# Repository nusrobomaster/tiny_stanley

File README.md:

# tiny_stanley
A minaturised version of our Standard robot, Stanley!

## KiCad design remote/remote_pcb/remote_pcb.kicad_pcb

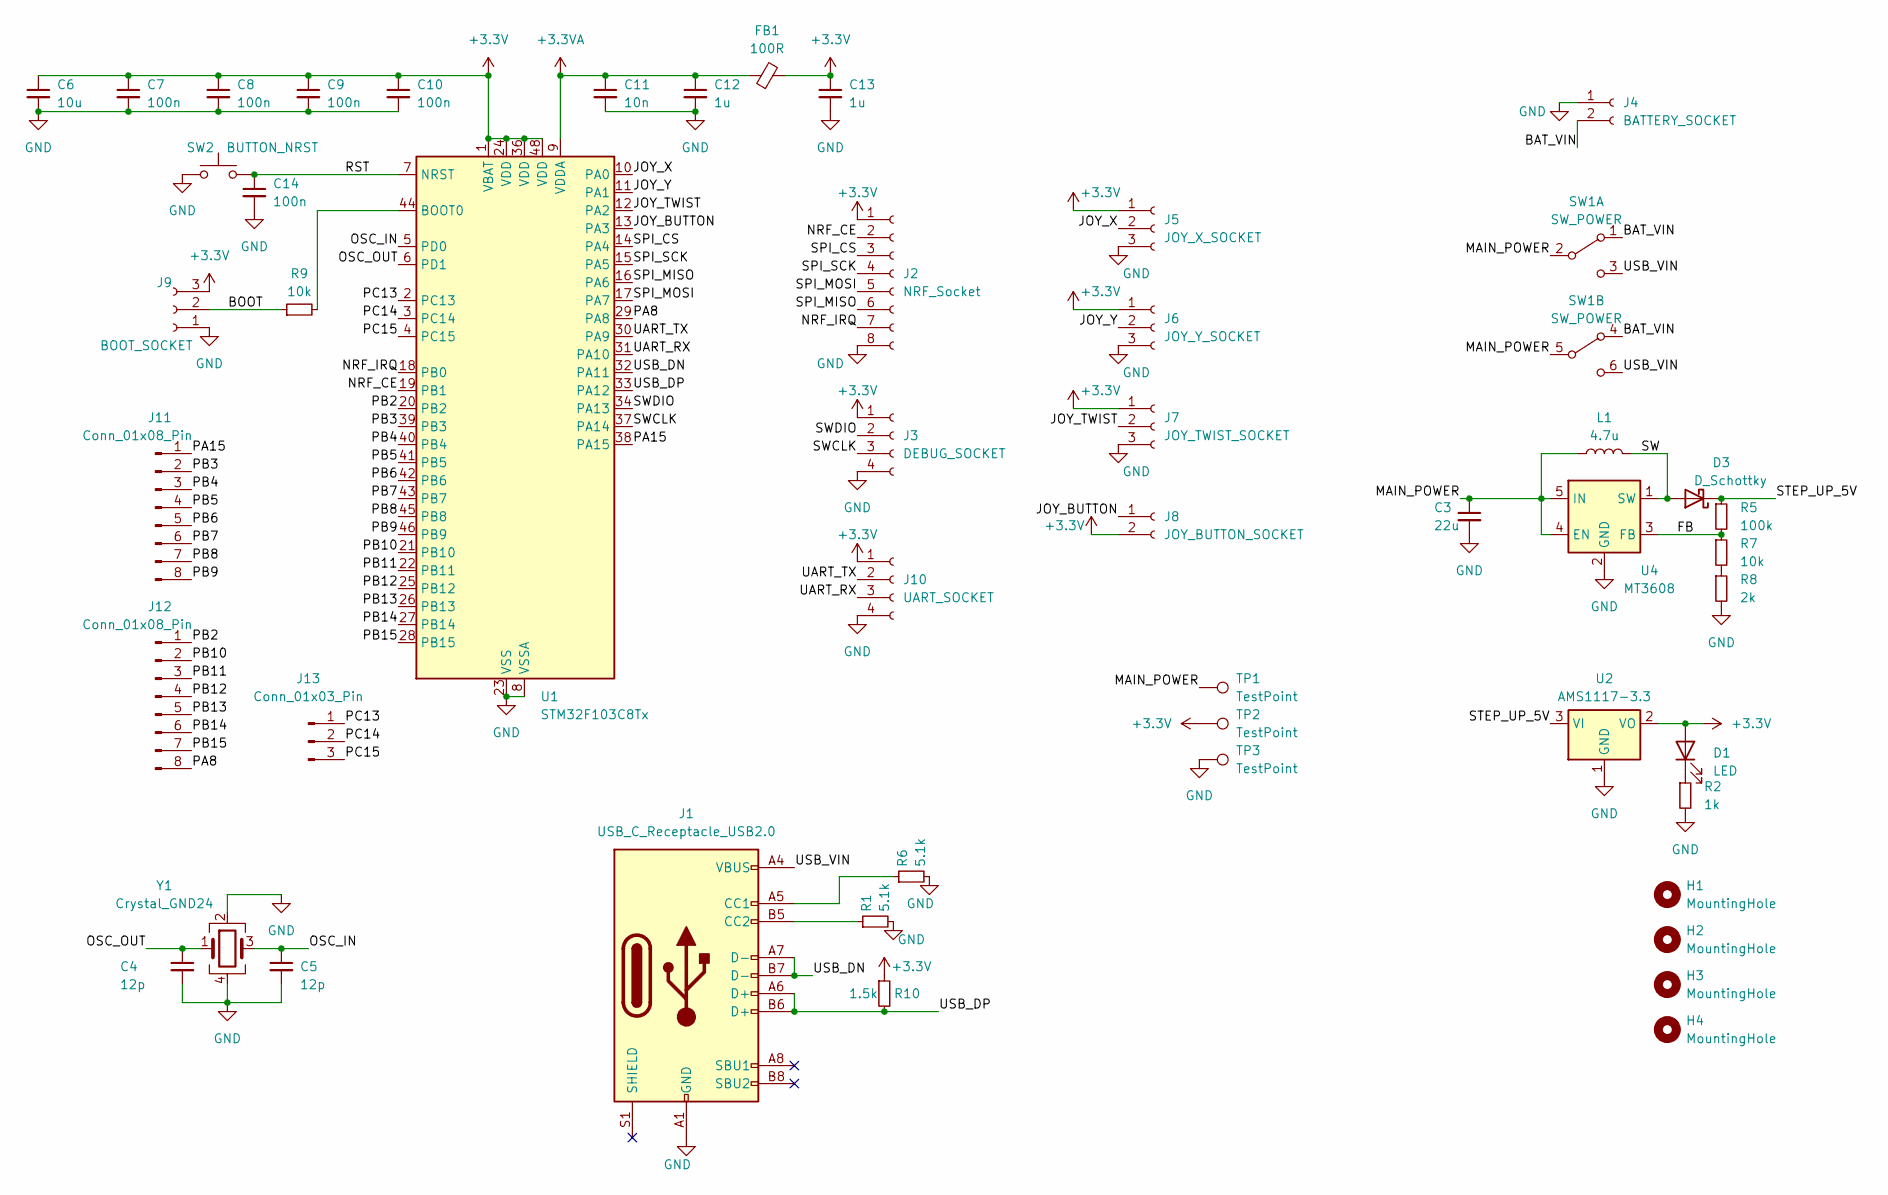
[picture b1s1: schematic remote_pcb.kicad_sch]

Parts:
C3: 22u; C_1210_3225Metric_Pad1.33x2.70mm_HandSolder
C4, C5: 12p; C_0402_1005Metric_Pad0.74x0.62mm_HandSolder
C6: 10u; C_0805_2012Metric_Pad1.18x1.45mm_HandSolder
C7, C8, C9, C10, C14: 100n; C_0402_1005Metric_Pad0.74x0.62mm_HandSolder
C11: 10n; C_0402_1005Metric_Pad0.74x0.62mm_HandSolder
C12, C13: 1u; C_0402_1005Metric_Pad0.74x0.62mm_HandSolder
D1: LED; LED_0603_1608Metric_Pad1.05x0.95mm_HandSolder
D3: D_Schottky; D_SOD-123
FB1: 100R; L_1206_3216Metric_Pad1.22x1.90mm_HandSolder
H1, H2, H3, H4: MountingHole; MountingHole_2.1mm
J1: USB_C_Receptacle_USB2.0; USB_C_Receptacle_HRO_TYPE-C-31-M-12
J2: NRF_Socket; NRF24L01
J3: DEBUG_SOCKET; PinHeader_1x04_P2.54mm_Vertical
J4: BATTERY_SOCKET; PinHeader_1x02_P2.54mm_Vertical
J5: JOY_X_SOCKET; JST_PH_S3B-PH-K_1x03_P2.00mm_Horizontal
J6: JOY_Y_SOCKET; JST_PH_S3B-PH-K_1x03_P2.00mm_Horizontal
J7: JOY_TWIST_SOCKET; JST_PH_S3B-PH-K_1x03_P2.00mm_Horizontal
J8: JOY_BUTTON_SOCKET; JST_PH_S2B-PH-K_1x02_P2.00mm_Horizontal
J9: BOOT_SOCKET; PinHeader_1x03_P2.54mm_Vertical
J10: UART_SOCKET; PinHeader_1x04_P2.54mm_Vertical
J11, J12: Conn_01x08_Pin; PinHeader_1x08_P2.54mm_Vertical
J13: Conn_01x03_Pin; PinHeader_1x03_P2.54mm_Vertical
L1: 4.7u; L_Coilcraft_XAL5020-XXX
R1, R6: 5.1k; R_0402_1005Metric_Pad0.72x0.64mm_HandSolder
R2: 1k; R_0402_1005Metric_Pad0.72x0.64mm_HandSolder
R5: 100k; R_0402_1005Metric_Pad0.72x0.64mm_HandSolder
R7, R9: 10k; R_0402_1005Metric_Pad0.72x0.64mm_HandSolder
R8: 2k; R_0402_1005Metric_Pad0.72x0.64mm_HandSolder
R10: 1.5k; R_0402_1005Metric_Pad0.72x0.64mm_HandSolder
SW1: SW_POWER; SW_CuK_JS202011AQN_DPDT_Angled
SW2: BUTTON_NRST; SW_Tactile_SPST_NO_Straight_CK_PTS636Sx25SMTRLFS
TP1, TP2, TP3: TestPoint; TestPoint_Pad_1.0x1.0mm
U1: STM32F103C8Tx; LQFP-48_7x7mm_P0.5mm
U2: AMS1117-3.3; SOT-223-3_TabPin2
U4: MT3608; SOT-23-6
Y1: Crystal_GND24; Crystal_SMD_3225-4Pin_3.2x2.5mm

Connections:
+3.3V: C6.1, C7.1, C8.1, C9.1, C10.1, C13.1, D1.2 (A), FB1.2, J2.1, J3.1, J5.1, J6.1, J7.1, J8.2, J9.3, J10.1, R10.1, TP2.1, U1.1 (VBAT), U1.24 (VDD), U1.36 (VDD), U1.48 (VDD), U2.2 (VO)
+3.3VA: C11.1, C12.1, FB1.1, U1.9 (VDDA)
/BAT_VIN: J4.2, SW1.1 (A), SW1.4 (A)
/BOOT: J9.2, R9.1
/FB: R5.2, R7.1, U4.3 (FB)
/JOY_BUTTON: J8.1, U1.13 (PA3)
/JOY_TWIST: J7.2, U1.12 (PA2)
/JOY_X: J5.2, U1.10 (PA0)
/JOY_Y: J6.2, U1.11 (PA1)
/MAIN_POWER: C3.1, L1.1, SW1.2 (B), SW1.5 (B), TP1.1, U4.4 (EN), U4.5 (IN)
/NRF_CE: J2.2, U1.19 (PB1)
/NRF_IRQ: J2.7, U1.18 (PB0)
/OSC_IN: C5.1, U1.5 (PD0), Y1.3
/OSC_OUT: C4.1, U1.6 (PD1), Y1.1
/PA8: J12.8, U1.29 (PA8)
/PA15: J11.1, U1.38 (PA15)
/PB2: J12.1, U1.20 (PB2)
/PB3: J11.2, U1.39 (PB3)
/PB4: J11.3, U1.40 (PB4)
/PB5: J11.4, U1.41 (PB5)
/PB6: J11.5, U1.42 (PB6)
/PB7: J11.6, U1.43 (PB7)
/PB8: J11.7, U1.45 (PB8)
/PB9: J11.8, U1.46 (PB9)
/PB10: J12.2, U1.21 (PB10)
/PB11: J12.3, U1.22 (PB11)
/PB12: J12.4, U1.25 (PB12)
/PB13: J12.5, U1.26 (PB13)
/PB14: J12.6, U1.27 (PB14)
/PB15: J12.7, U1.28 (PB15)
/PC13: J13.1, U1.2 (PC13)
/PC14: J13.2, U1.3 (PC14)
/PC15: J13.3, U1.4 (PC15)
/RST: C14.1, SW2.2, U1.7 (NRST)
/SPI_CS: J2.3, U1.14 (PA4)
/SPI_MISO: J2.6, U1.16 (PA6)
/SPI_MOSI: J2.5, U1.17 (PA7)
/SPI_SCK: J2.4, U1.15 (PA5)
/STEP_UP_5V: D3.1 (K), R5.1, U2.3 (VI)
/SW: D3.2 (A), L1.2, U4.1 (SW)
/SWCLK: J3.3, U1.37 (PA14)
/SWDIO: J3.2, U1.34 (PA13)
/UART_RX: J10.3, U1.31 (PA10)
/UART_TX: J10.2, U1.30 (PA9)
/USB_DN: J1.A7 (D-), J1.B7 (D-), U1.32 (PA11)
/USB_DP: J1.A6 (D+), J1.B6 (D+), R10.2, U1.33 (PA12)
/USB_VIN: J1.A4 (VBUS), J1.A9 (VBUS), J1.B4 (VBUS), J1.B9 (VBUS), SW1.3 (C), SW1.6 (C)
GND: C3.2, C4.2, C5.2, C6.2, C7.2, C8.2, C9.2, C10.2, C11.2, C12.2, C13.2, C14.2, J1.A1 (GND), J1.A12 (GND), J1.B1 (GND), J1.B12 (GND), J2.8, J3.4, J4.1, J5.3, J6.3, J7.3, J9.1, J10.4, R1.2, R2.2, R6.2, R8.2, SW2.1, TP3.1, U1.8 (VSSA), U1.23 (VSS), U1.35 (VSS), U1.47 (VSS), U2.1 (GND), U4.2 (GND), Y1.2, Y1.4
unnamed: D1.1 (K), R2.1
unnamed: J1.A5 (CC1), R6.1
unnamed: J1.B5 (CC2), R1.1
unnamed: R7.2, R8.1
unnamed: R9.2, U1.44 (BOOT0)

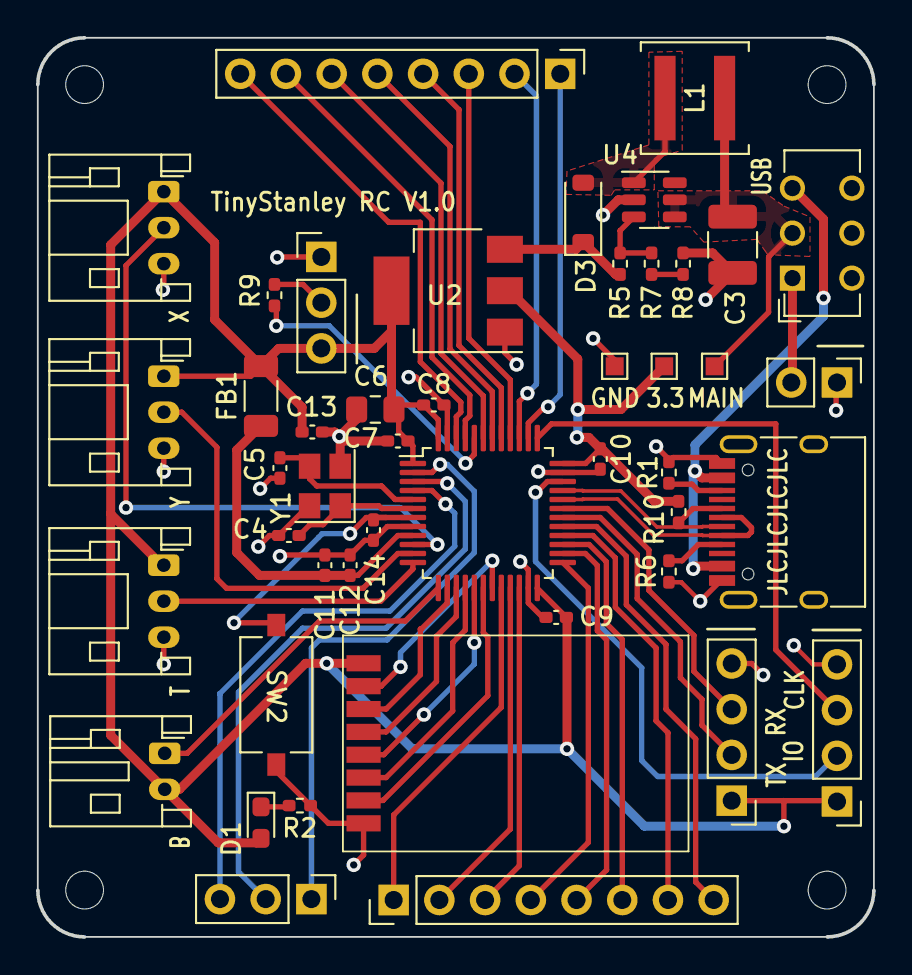
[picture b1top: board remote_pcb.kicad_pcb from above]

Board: 2 copper layers, 46.5 x 50.0 mm, 50 parts (0 on the bottom side), 53 nets.

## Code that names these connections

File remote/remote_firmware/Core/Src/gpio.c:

/* USER CODE BEGIN Header */
/**
  ******************************************************************************
  * @file    gpio.c
  * @brief   This file provides code for the configuration
  *          of all used GPIO pins.
  ******************************************************************************
  * @attention
  *
  * Copyright (c) 2023 STMicroelectronics.
  * All rights reserved.
  *
  * This software is licensed under terms that can be found in the LICENSE file
  * in the root directory of this software component.
  * If no LICENSE file comes with this software, it is provided AS-IS.
  *
  ******************************************************************************
  */
/* USER CODE END Header */

/* Includes ------------------------------------------------------------------*/
#include "gpio.h"

/* USER CODE BEGIN 0 */

/* USER CODE END 0 */

/*----------------------------------------------------------------------------*/
/* Configure GPIO                                                             */
/*----------------------------------------------------------------------------*/
/* USER CODE BEGIN 1 */

/* USER CODE END 1 */

/** Configure pins as
        * Analog
        * Input
        * Output
        * EVENT_OUT
        * EXTI
        * Free pins are configured automatically as Analog (this feature is enabled through
        * the Code Generation settings)
*/
void MX_GPIO_Init(void)
{

  GPIO_InitTypeDef GPIO_InitStruct = {0};

  /* GPIO Ports Clock Enable */
  __HAL_RCC_GPIOC_CLK_ENABLE();
  __HAL_RCC_GPIOD_CLK_ENABLE();
  __HAL_RCC_GPIOA_CLK_ENABLE();
  __HAL_RCC_GPIOB_CLK_ENABLE();

  /*Configure GPIO pin Output Level */
  HAL_GPIO_WritePin(SPI1_CS_GPIO_Port, SPI1_CS_Pin, GPIO_PIN_RESET);

  /*Configure GPIO pin Output Level */
  HAL_GPIO_WritePin(NRF_CE_GPIO_Port, NRF_CE_Pin, GPIO_PIN_RESET);

  /*Configure GPIO pins : PC13 PC14 PC15 */
  GPIO_InitStruct.Pin = GPIO_PIN_13|GPIO_PIN_14|GPIO_PIN_15;
  GPIO_InitStruct.Mode = GPIO_MODE_ANALOG;
  HAL_GPIO_Init(GPIOC, &GPIO_InitStruct);

  /*Configure GPIO pin : PtPin */
  GPIO_InitStruct.Pin = JOY_BUTTON_Pin;
  GPIO_InitStruct.Mode = GPIO_MODE_INPUT;
  GPIO_InitStruct.Pull = GPIO_NOPULL;
  HAL_GPIO_Init(JOY_BUTTON_GPIO_Port, &GPIO_InitStruct);

  /*Configure GPIO pin : PtPin */
  GPIO_InitStruct.Pin = SPI1_CS_Pin;
  GPIO_InitStruct.Mode = GPIO_MODE_OUTPUT_PP;
  GPIO_InitStruct.Pull = GPIO_NOPULL;
  GPIO_InitStruct.Speed = GPIO_SPEED_FREQ_LOW;
  HAL_GPIO_Init(SPI1_CS_GPIO_Port, &GPIO_InitStruct);

  /*Configure GPIO pin : PtPin */
  GPIO_InitStruct.Pin = NRF_IRQ_Pin;
  GPIO_InitStruct.Mode = GPIO_MODE_IT_RISING;
  GPIO_InitStruct.Pull = GPIO_NOPULL;
  HAL_GPIO_Init(NRF_IRQ_GPIO_Port, &GPIO_InitStruct);

  /*Configure GPIO pin : PtPin */
  GPIO_InitStruct.Pin = NRF_CE_Pin;
  GPIO_InitStruct.Mode = GPIO_MODE_OUTPUT_PP;
  GPIO_InitStruct.Pull = GPIO_NOPULL;
  GPIO_InitStruct.Speed = GPIO_SPEED_FREQ_LOW;
  HAL_GPIO_Init(NRF_CE_GPIO_Port, &GPIO_InitStruct);

  /*Configure GPIO pins : PB2 PB10 PB11 PB12
                           PB13 PB14 PB15 PB3
                           PB4 PB5 PB6 PB7
                           PB8 PB9 */
  GPIO_InitStruct.Pin = GPIO_PIN_2|GPIO_PIN_10|GPIO_PIN_11|GPIO_PIN_12
                          |GPIO_PIN_13|GPIO_PIN_14|GPIO_PIN_15|GPIO_PIN_3
                          |GPIO_PIN_4|GPIO_PIN_5|GPIO_PIN_6|GPIO_PIN_7
                          |GPIO_PIN_8|GPIO_PIN_9;
  GPIO_InitStruct.Mode = GPIO_MODE_ANALOG;
  HAL_GPIO_Init(GPIOB, &GPIO_InitStruct);

  /*Configure GPIO pins : PA8 PA9 PA10 PA15 */
  GPIO_InitStruct.Pin = GPIO_PIN_8|GPIO_PIN_9|GPIO_PIN_10|GPIO_PIN_15;
  GPIO_InitStruct.Mode = GPIO_MODE_ANALOG;
  HAL_GPIO_Init(GPIOA, &GPIO_InitStruct);

  /* EXTI interrupt init*/
  HAL_NVIC_SetPriority(EXTI0_IRQn, 0, 0);
  HAL_NVIC_EnableIRQ(EXTI0_IRQn);

}

/* USER CODE BEGIN 2 */

/* USER CODE END 2 */

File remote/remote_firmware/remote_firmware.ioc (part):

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Mcu.Name=STM32F103C(8-B)Tx
Mcu.Package=LQFP48
Mcu.UserName=STM32F103C8Tx
PA0-WKUP.Signal=ADCx_IN0
PA1.Signal=ADCx_IN1
PA11.Mode=Device
PA11.Signal=USB_DM
PA12.Mode=Device
PA12.Signal=USB_DP
PA13.Mode=Serial_Wire
PA13.Signal=SYS_JTMS-SWDIO
PA14.Mode=Serial_Wire
PA14.Signal=SYS_JTCK-SWCLK
PA2.Signal=ADCx_IN2
PA3.GPIOParameters=GPIO_Label
PA3.GPIO_Label=JOY_BUTTON
PA3.Signal=GPIO_Input
PA4.GPIOParameters=GPIO_Label
PA4.GPIO_Label=SPI1_CS
PA4.Signal=GPIO_Output
PA5.Mode=Full_Duplex_Master
PA5.Signal=SPI1_SCK
PA6.Mode=Full_Duplex_Master
PA6.Signal=SPI1_MISO
PA7.Mode=Full_Duplex_Master
PA7.Signal=SPI1_MOSI
PB0.GPIOParameters=GPIO_Label
PB0.GPIO_Label=NRF_IRQ
PB0.Signal=GPXTI0
PB1.GPIOParameters=GPIO_Label
PB1.GPIO_Label=NRF_CE
PB1.Signal=GPIO_Output
PD0-OSC_IN.Mode=HSE-External-Oscillator
PD0-OSC_IN.Signal=RCC_OSC_IN
PD1-OSC_OUT.Mode=HSE-External-Oscillator
PD1-OSC_OUT.Signal=RCC_OSC_OUT
RCC.SYSCLKFreq_VALUE=48000000
RCC.SYSCLKSource=RCC_SYSCLKSOURCE_PLLCLK
board=custom

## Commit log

2023-12-23 added remote SolidWorks and stl files
2023-12-23 removed one wrong file
